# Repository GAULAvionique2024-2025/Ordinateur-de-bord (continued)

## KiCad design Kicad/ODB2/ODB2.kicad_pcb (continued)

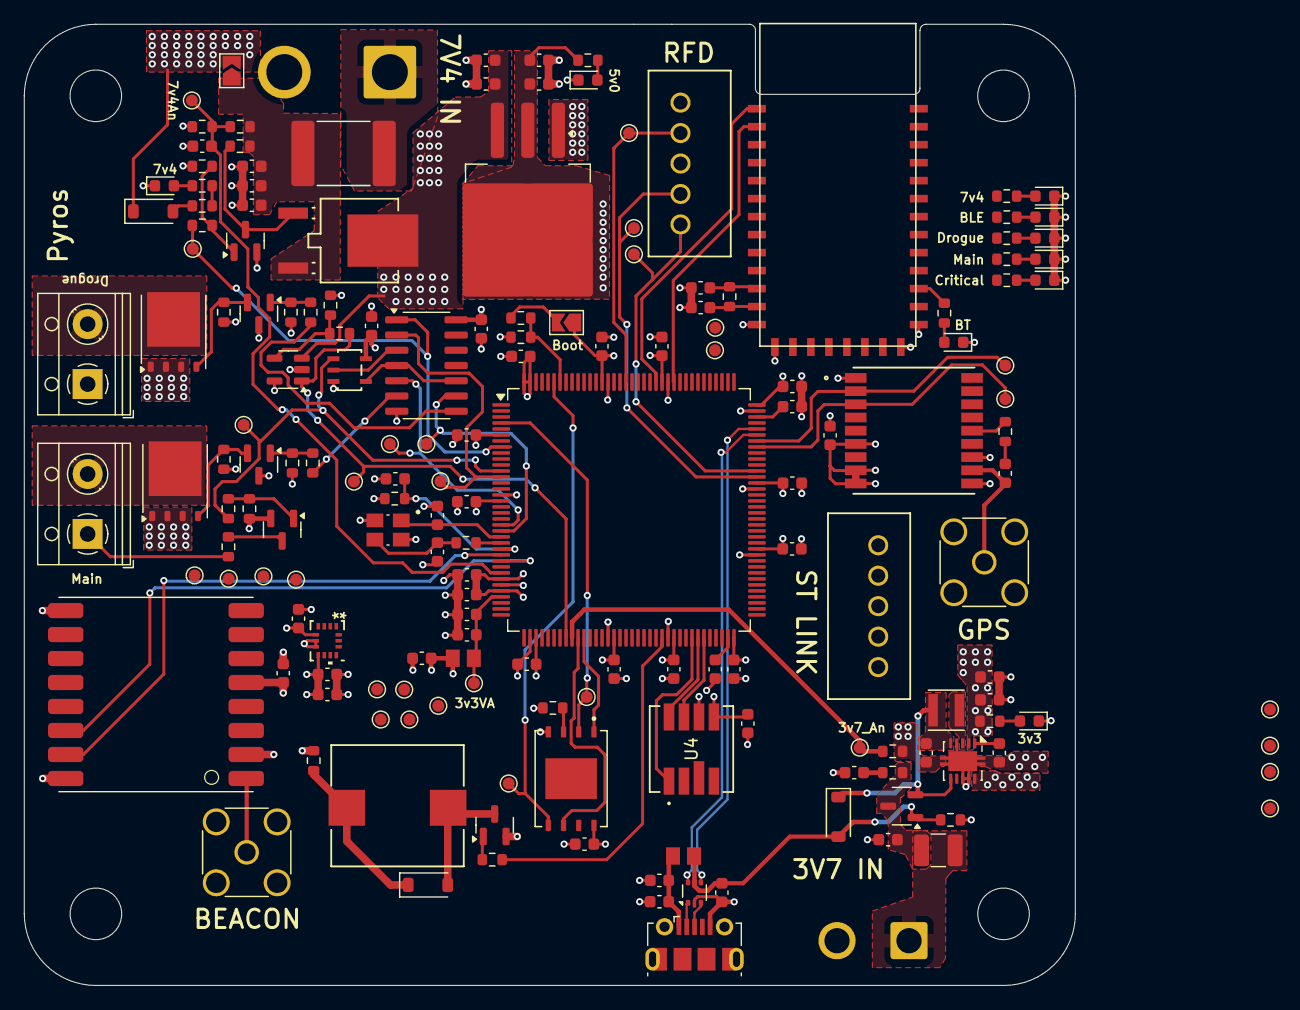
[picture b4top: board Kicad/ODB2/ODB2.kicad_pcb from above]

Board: 4 copper layers, 87.6 x 80.1 mm, 176 parts (0 on the bottom side), 101 nets.

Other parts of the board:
7v4_LED1, 7v4_LED2: GREEN; LED_0603_1608Metric

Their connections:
GND: 7v4_LED1.1 (K), 7v4_LED2.1 (K); also elsewhere on the board
unnamed 28: 7v4_LED1.2 (A); also elsewhere on the board
unnamed 29: 7v4_LED2.2 (A); also elsewhere on the board

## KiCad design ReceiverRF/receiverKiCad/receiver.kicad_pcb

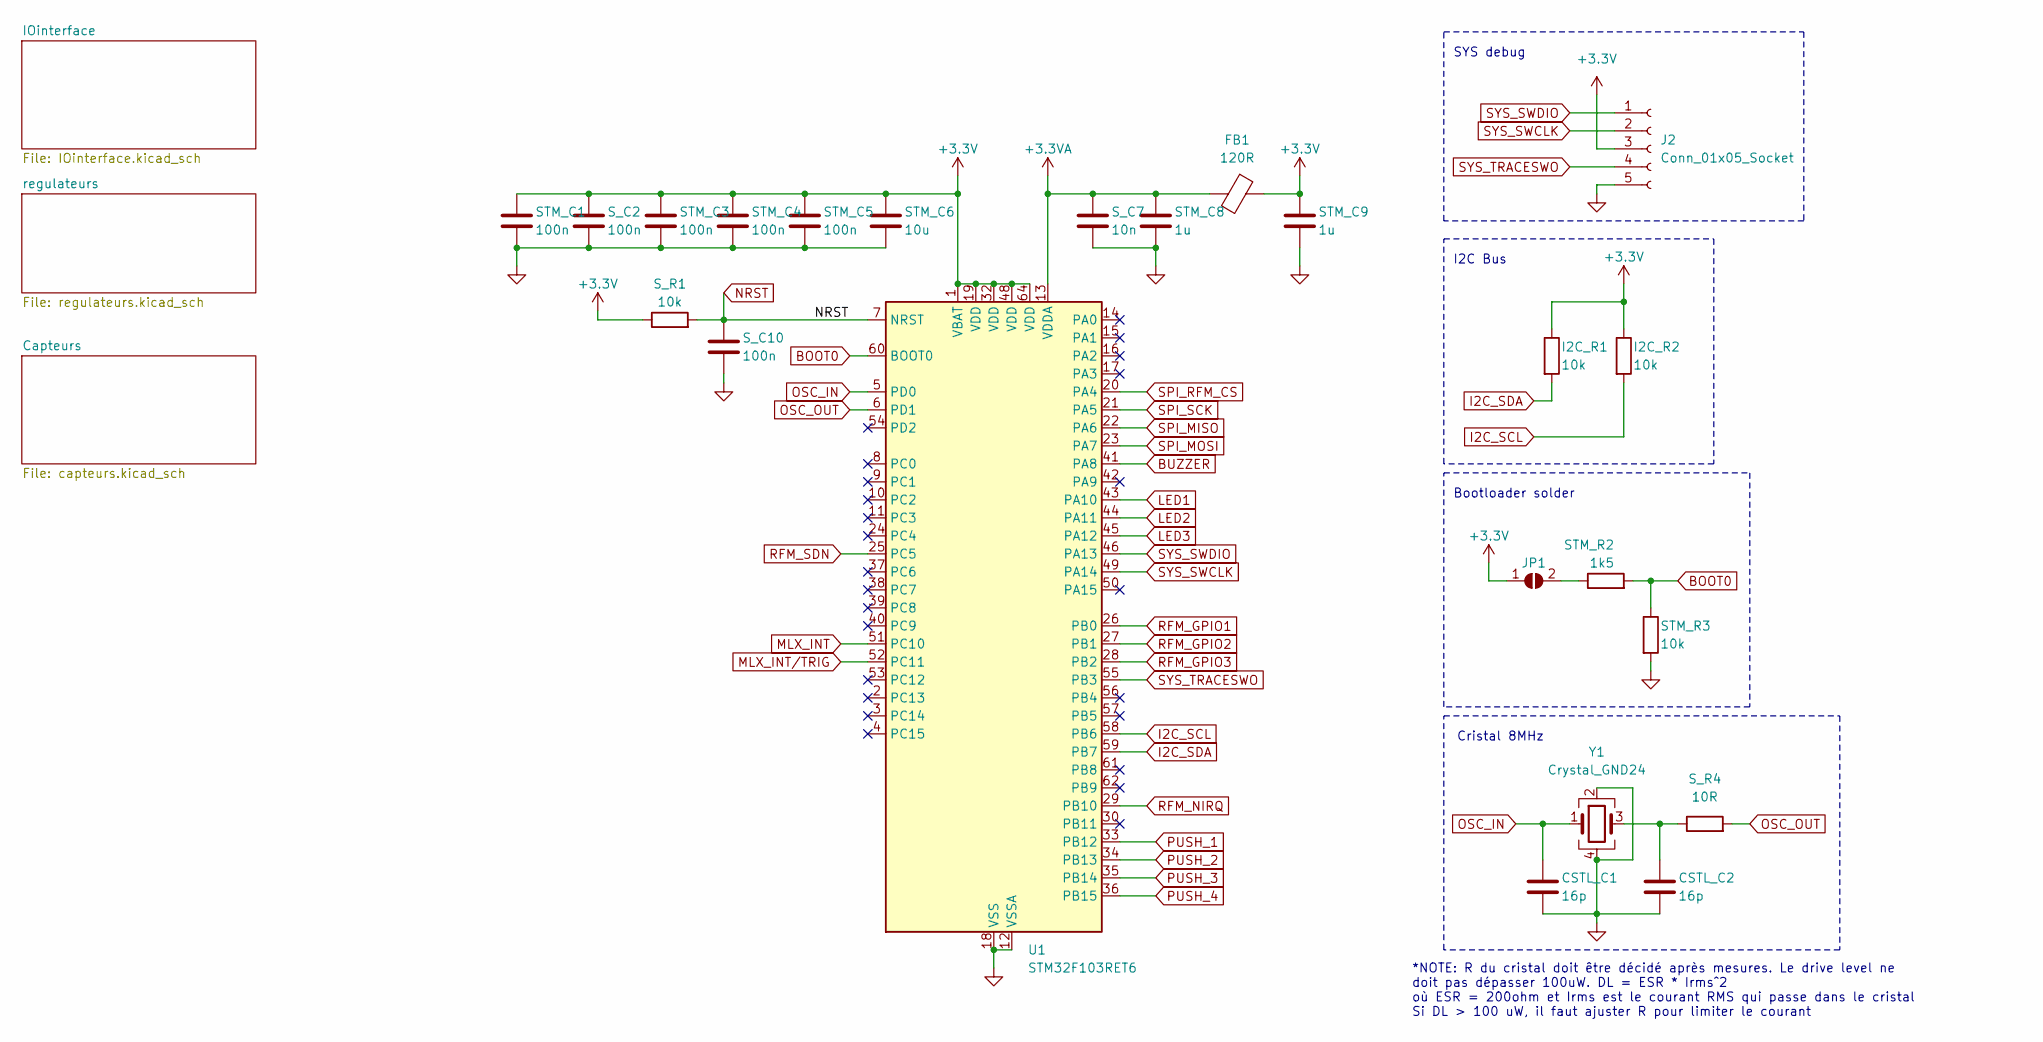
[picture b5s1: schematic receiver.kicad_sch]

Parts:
CSTL_C1, CSTL_C2: 16p; C_0402_1005Metric
FB1: 120R; Ferrite_0603
I2C_R1, I2C_R2: 10k; R_0402_1005Metric
J2: Conn_01x05_Socket; PinHeader_1x05_P2.00mm_Vertical
JP1: SolderJumper_2_Open; SolderJumper-2_P1.3mm_Open_TrianglePad1.0x1.5mm
STM_C1, STM_C3, STM_C4, STM_C5: 100n; C_0402_1005Metric
STM_C6: 10u; C_1206_3216Metric
STM_C8, STM_C9: 1u; C_0603_1608Metric
STM_R2: 1k5; R_0402_1005Metric
STM_R3: 10k; R_0402_1005Metric
S_C2, S_C10: 100n; C_0402_1005Metric
S_C7: 10n; C_0402_1005Metric
S_R1: 10k; R_0402_1005Metric
S_R4: 10R; R_0402_1005Metric
U1: STM32F103RET6; LQFP64-10x10mm
Y1: Crystal_GND24; Crystal

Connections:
+3.3V: FB1.1, I2C_R1.1, I2C_R2.1, J2.3, JP1.1 (A), STM_C1.1, STM_C3.1, STM_C4.1, STM_C5.1, STM_C6.1, STM_C9.1, S_C2.1, S_R1.1, U1.1 (VBAT), U1.19 (VDD), U1.32 (VDD), U1.48 (VDD), U1.64 (VDD); also elsewhere on the board
+3.3VA: FB1.2, STM_C8.1, S_C7.1, U1.13 (VDDA)
BOOT0: STM_R2.2, STM_R3.1, U1.60 (BOOT0)
BUZZER: U1.41 (PA8); also elsewhere on the board
GND: CSTL_C1.2, CSTL_C2.2, J2.5, STM_C1.2, STM_C3.2, STM_C4.2, STM_C5.2, STM_C6.2, STM_C8.2, STM_C9.2, STM_R3.2, S_C2.2, S_C7.2, S_C10.2, U1.12 (VSSA), U1.18 (VSS), U1.31 (VSS), U1.47 (VSS), U1.63 (VSS), Y1.2, Y1.4; also elsewhere on the board
I2C_SCL: I2C_R2.2, U1.58 (PB6); also elsewhere on the board
I2C_SDA: I2C_R1.2, U1.59 (PB7); also elsewhere on the board
LED1: U1.43 (PA10); also elsewhere on the board
LED2: U1.44 (PA11); also elsewhere on the board
LED3: U1.45 (PA12); also elsewhere on the board
MLX_INT: U1.51 (PC10); also elsewhere on the board
MLX_INT/TRIG: U1.52 (PC11); also elsewhere on the board
NRST: S_C10.1, S_R1.2, U1.7 (NRST)
unnamed: CSTL_C2.1, S_R4.1, Y1.3
unnamed: JP1.2 (B), STM_R2.1
OSC_IN: CSTL_C1.1, U1.5 (PD0), Y1.1
OSC_OUT: S_R4.2, U1.6 (PD1)
PUSH_1: U1.33 (PB12); also elsewhere on the board
PUSH_2: U1.34 (PB13); also elsewhere on the board
PUSH_3: U1.35 (PB14); also elsewhere on the board
PUSH_4: U1.36 (PB15); also elsewhere on the board
RFM_GPIO1: U1.26 (PB0); also elsewhere on the board
RFM_GPIO2: U1.27 (PB1); also elsewhere on the board
RFM_GPIO3: U1.28 (PB2); also elsewhere on the board
RFM_NIRQ: U1.29 (PB10); also elsewhere on the board
RFM_SDN: U1.25 (PC5); also elsewhere on the board
SPI_MISO: U1.22 (PA6); also elsewhere on the board
SPI_MOSI: U1.23 (PA7); also elsewhere on the board
SPI_RFM_CS: U1.20 (PA4); also elsewhere on the board
SPI_SCK: U1.21 (PA5); also elsewhere on the board
SYS_SWCLK: J2.2, U1.49 (PA14)
SYS_SWDIO: J2.1, U1.46 (PA13)
SYS_TRACESWO: J2.4, U1.55 (PB3)

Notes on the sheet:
I2C Bus
Cristal 8MHz
Bootloader solder
SYS debug
*NOTE: R du cristal doit être décidé après mesures. Le drive level ne doit pas dépasser 100uW. DL = ESR * Irms^2 où ESR = 200ohm et Irms est le courant RMS qui passe dans le cristal Si DL > 100 uW, il faut ajuster R pour limiter le courant

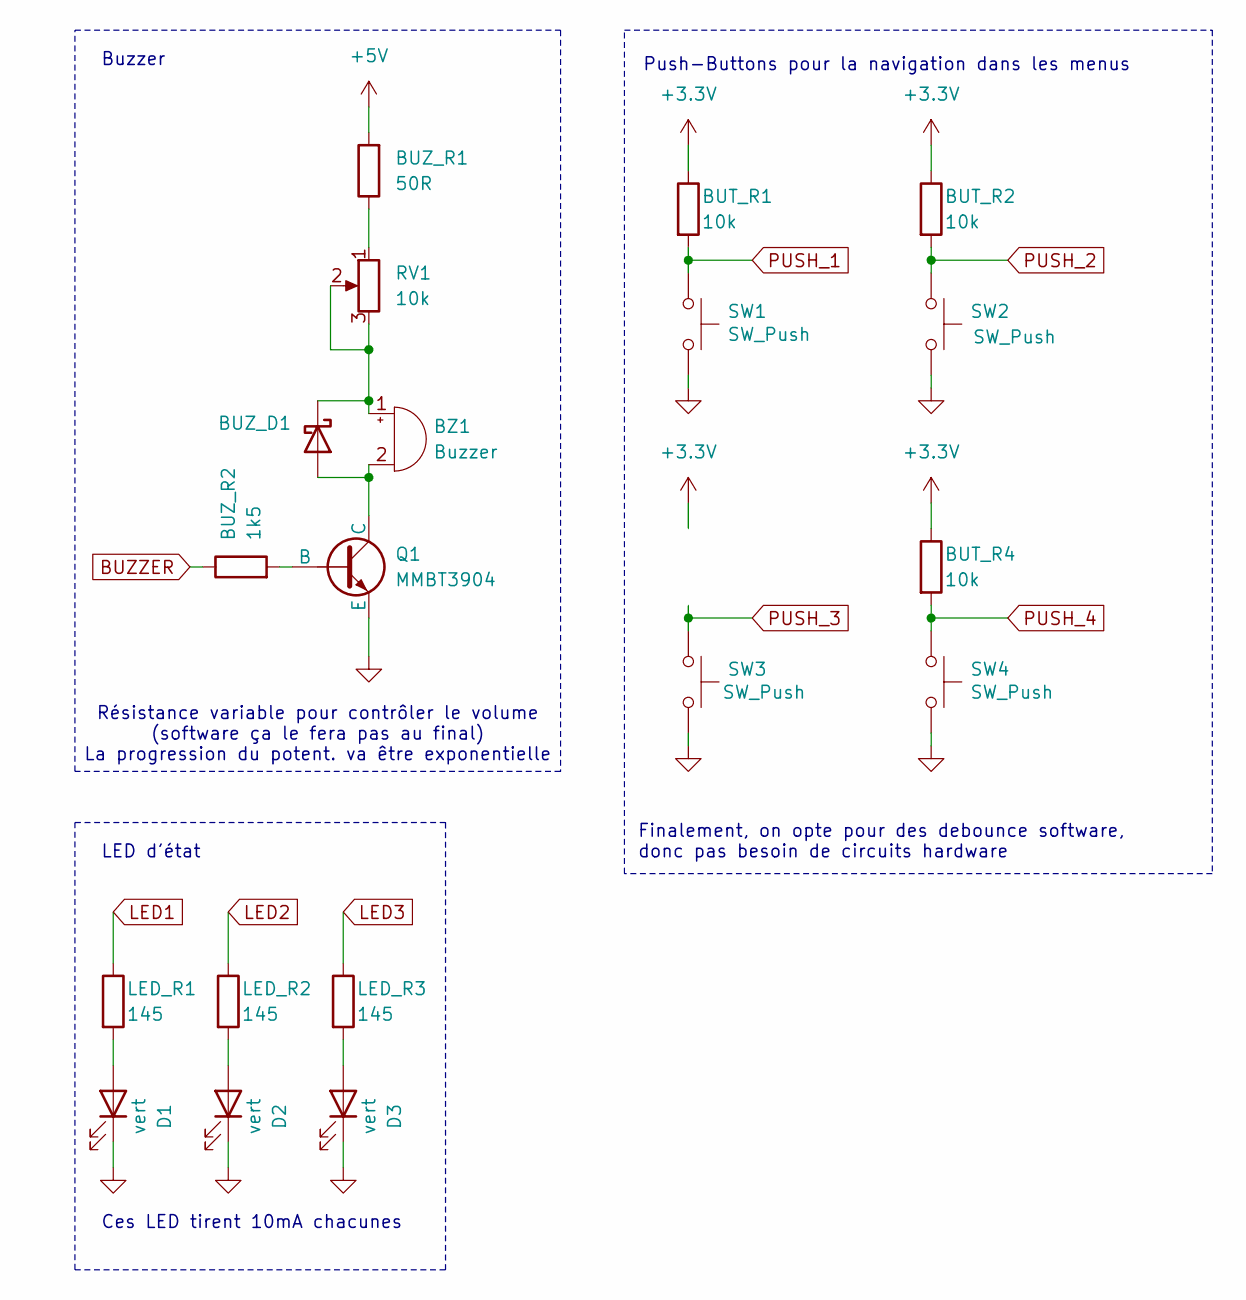
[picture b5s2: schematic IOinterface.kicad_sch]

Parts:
BUT_R1, BUT_R2, BUT_R4: 10k; R_0402_1005Metric
BUZ_D1: D_SOD-123
BUZ_R1: 50R; R_1206_3216Metric
BUZ_R2: 1k5; R_0402_1005Metric
BZ1: Buzzer; Buzzer_D14mm_H7mm_P10mm
D1, D2, D3: vert; LTST-C170GKT
LED_R1, LED_R2, LED_R3: 145; R_1206_3216Metric
Q1: MMBT3904; SOT-23
RV1: 10k; Potentiometer_Alps_RK09K_Single_Vertical
SW1, SW2, SW3, SW4: SW_Push; SW_PUSH_6mm_H4.3mm

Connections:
+3.3V: BUT_R1.1, BUT_R2.1, BUT_R4.1; also elsewhere on the board
+5V: BUZ_R1.2; also elsewhere on the board
BUZZER: BUZ_R2.1; also elsewhere on the board
GND: D1.1 (K), D2.1 (K), D3.1 (K), Q1.3 (E), SW1.2, SW2.2, SW3.2, SW4.2; also elsewhere on the board
LED1: LED_R1.1; also elsewhere on the board
LED2: LED_R2.1; also elsewhere on the board
LED3: LED_R3.1; also elsewhere on the board
unnamed: BUZ_D1.2 (A), BZ1.2 (+), Q1.1 (C)
unnamed: BUZ_D1.1 (K), BZ1.1 (-), RV1.2, RV1.3
unnamed: BUZ_R1.1, RV1.1
unnamed: D1.2 (A), LED_R1.2
unnamed: D2.2 (A), LED_R2.2
unnamed: D3.2 (A), LED_R3.2
unnamed: BUZ_R2.2, Q1.2 (B)
PUSH_1: BUT_R1.2, SW1.1; also elsewhere on the board
PUSH_2: BUT_R2.2, SW2.1; also elsewhere on the board
PUSH_3: SW3.1; also elsewhere on the board
PUSH_4: BUT_R4.2, SW4.1; also elsewhere on the board

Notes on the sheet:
Finalement, on opte pour des debounce software, donc pas besoin de circuits hardware
Résistance variable pour contrôler le volume (software ça le fera pas au final) La progression du potent. va être exponentielle
Buzzer
Ces LED tirent 10mA chacunes
Push-Buttons pour la navigation dans les menus
LED d'état

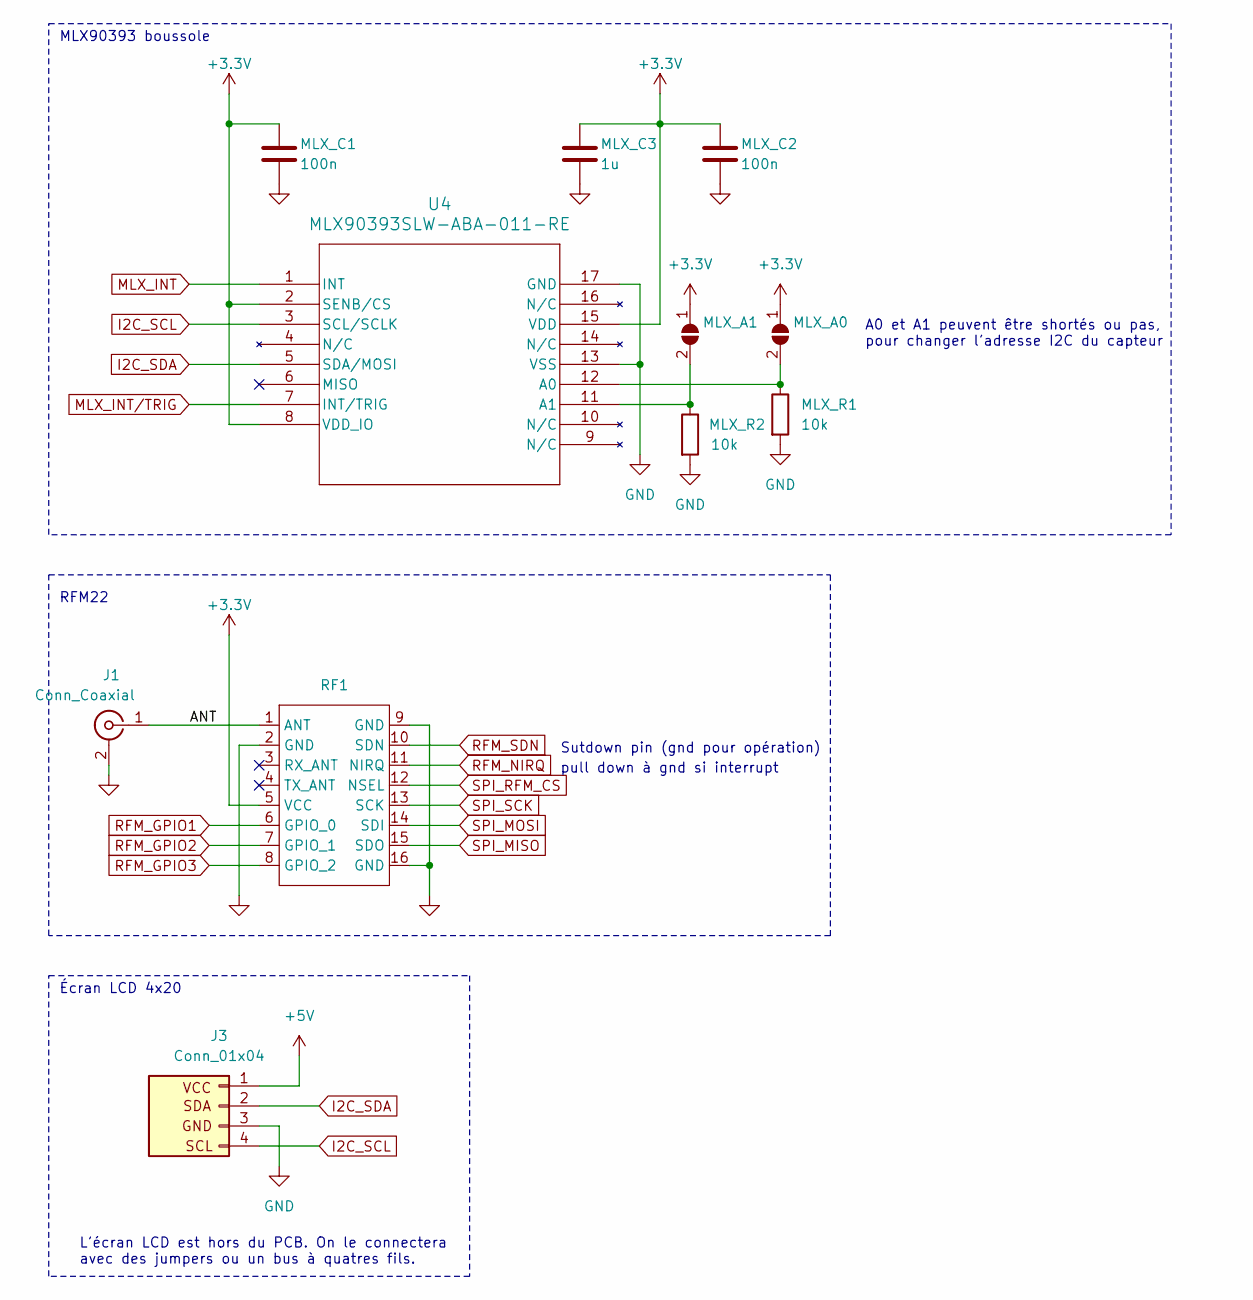
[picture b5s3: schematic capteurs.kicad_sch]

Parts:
J1: Conn_Coaxial; SMA_90deg
J3: Conn_01x04; PinHeader_1x04_P2.00mm_Vertical
MLX_A0, MLX_A1: 0; SolderJumper-2_P1.3mm_Open_TrianglePad1.0x1.5mm
MLX_C1, MLX_C2: 100n; C_0402_1005Metric
MLX_C3: 1u; C_0603_1608Metric
MLX_R1, MLX_R2: 10k; R_0402_1005Metric
RF1: RFM22b-S2
U4: MLX90393SLW-ABA-011-RE; QFN-16_MLX90393_MEL-L

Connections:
+3.3V: MLX_A0.1 (A), MLX_A1.1 (A), MLX_C1.1, MLX_C2.1, MLX_C3.1, RF1.5 (VCC), U4.2 (SENB/CS), U4.8 (VDD_IO), U4.15 (VDD); also elsewhere on the board
+5V: J3.1 (GND); also elsewhere on the board
/Capteurs/ANT: J1.1 (In), RF1.1 (ANT)
GND: J1.2 (Ext), J3.3 (SDA), MLX_C1.2, MLX_C2.2, MLX_C3.2, MLX_R1.2, MLX_R2.2, RF1.2 (GND), RF1.9 (GND), RF1.16 (GND), U4.13 (VSS), U4.17 (GND); also elsewhere on the board
I2C_SCL: J3.4 (SCL), U4.3 (SCL/SCLK); also elsewhere on the board
I2C_SDA: J3.2 (VCC), U4.5 (SDA/MOSI); also elsewhere on the board
MLX_INT: U4.1 (INT); also elsewhere on the board
MLX_INT/TRIG: U4.7 (INT/TRIG); also elsewhere on the board
unnamed: MLX_A0.2 (B), MLX_R1.1, U4.12 (A0)
unnamed: MLX_A1.2 (B), MLX_R2.1, U4.11 (A1)
RFM_GPIO1: RF1.6 (GPIO_0); also elsewhere on the board
RFM_GPIO2: RF1.7 (GPIO_1); also elsewhere on the board
RFM_GPIO3: RF1.8 (GPIO_2); also elsewhere on the board
RFM_NIRQ: RF1.11 (NIRQ); also elsewhere on the board
RFM_SDN: RF1.10 (SDN); also elsewhere on the board
SPI_MISO: RF1.15 (SDO); also elsewhere on the board
SPI_MOSI: RF1.14 (SDI); also elsewhere on the board
SPI_RFM_CS: RF1.12 (NSEL); also elsewhere on the board
SPI_SCK: RF1.13 (SCK); also elsewhere on the board

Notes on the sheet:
L'écran LCD est hors du PCB. On le connectera avec des jumpers ou un bus à quatres fils.
pull down à gnd si interrupt
Sutdown pin (gnd pour opération)
MLX90393 boussole
RFM22
A0 et A1 peuvent être shortés ou pas, pour changer l'adresse I2C du capteur
Écran LCD 4x20

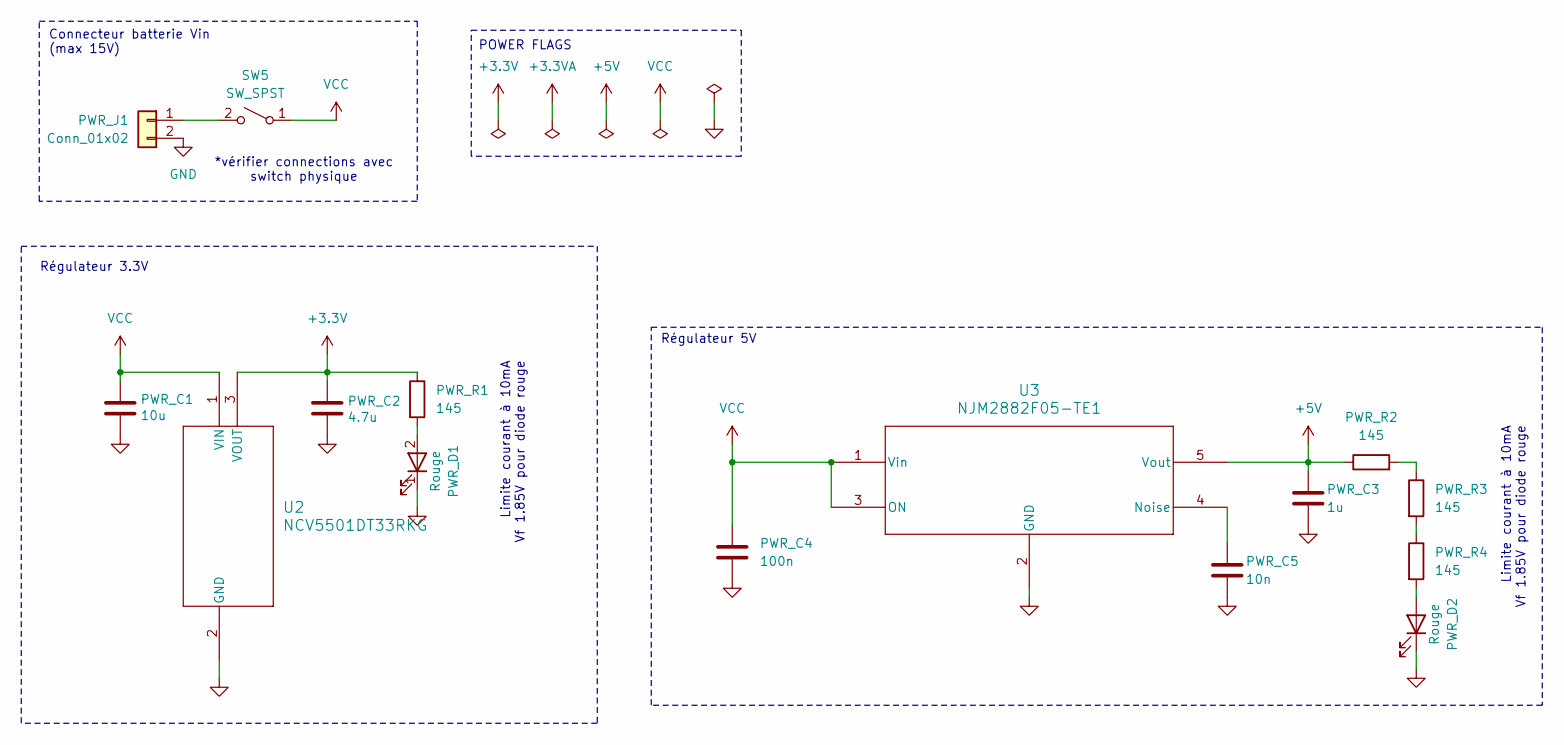
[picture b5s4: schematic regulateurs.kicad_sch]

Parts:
PWR_C1: 10u; C_1206_3216Metric
PWR_C2: 4.7u; C_0603_1608Metric
PWR_C3: 1u; C_0603_1608Metric
PWR_C4: 100n; C_0402_1005Metric
PWR_C5: 10n; C_0402_1005Metric
PWR_D1, PWR_D2: Rouge; LTST-C190EKT
PWR_J1: Conn_01x02; PinHeader_1x02_P2.00mm_Vertical
PWR_R1, PWR_R2, PWR_R3, PWR_R4: 145; R_1206_3216Metric
SW5: SW_SPST; SW_1MS02Q_CNK
U2: NCV5501DT33RKG; DPAK-3_ONS-M
U3: NJM2882F05-TE1; SOT-23-5

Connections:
+3.3V: PWR_C2.1, PWR_R1.1, U2.3 (VOUT); also elsewhere on the board
+5V: PWR_C3.1, PWR_R2.1, U3.5 (Vout); also elsewhere on the board
GND: PWR_C1.2, PWR_C2.2, PWR_C3.2, PWR_C4.2, PWR_C5.2, PWR_D1.1 (K), PWR_D2.1 (K), PWR_J1.2, U2.2 (GND), U3.2 (GND); also elsewhere on the board
unnamed: PWR_D1.2 (A), PWR_R1.2
unnamed: PWR_D2.2 (A), PWR_R4.2
unnamed: PWR_J1.1, SW5.2 (B)
unnamed: PWR_R2.2, PWR_R3.1
unnamed: PWR_R3.2, PWR_R4.1
unnamed: PWR_C5.1, U3.4 (Noise)
VCC: PWR_C1.1, PWR_C4.1, SW5.1 (A), U2.1 (VIN), U3.1 (Vin), U3.3 (ON)

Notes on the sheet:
Limite courant à 10mA Vf 1.85V pour diode rouge
Connecteur batterie Vin (max 15V)
POWER FLAGS
Régulateur 5V
*vérifier connections avec switch physique
Régulateur 3.3V

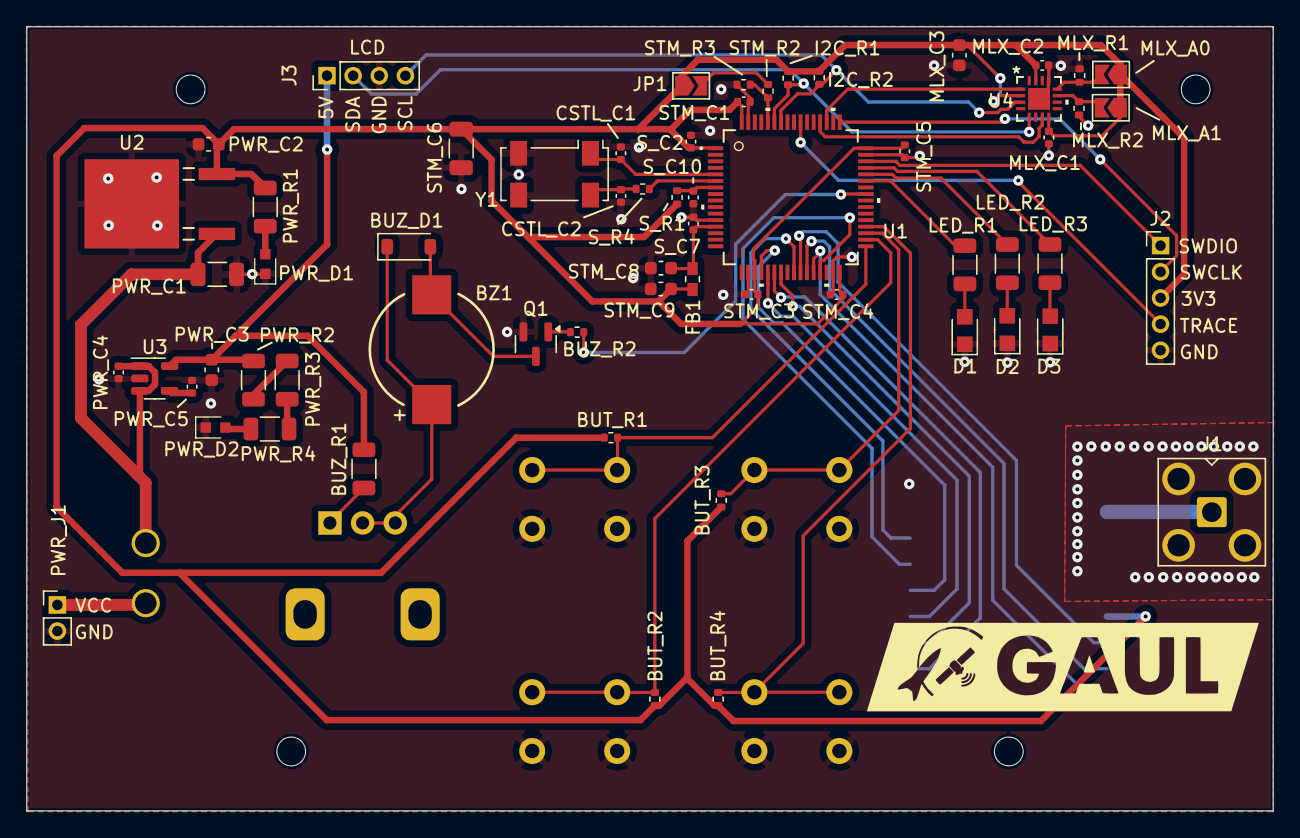
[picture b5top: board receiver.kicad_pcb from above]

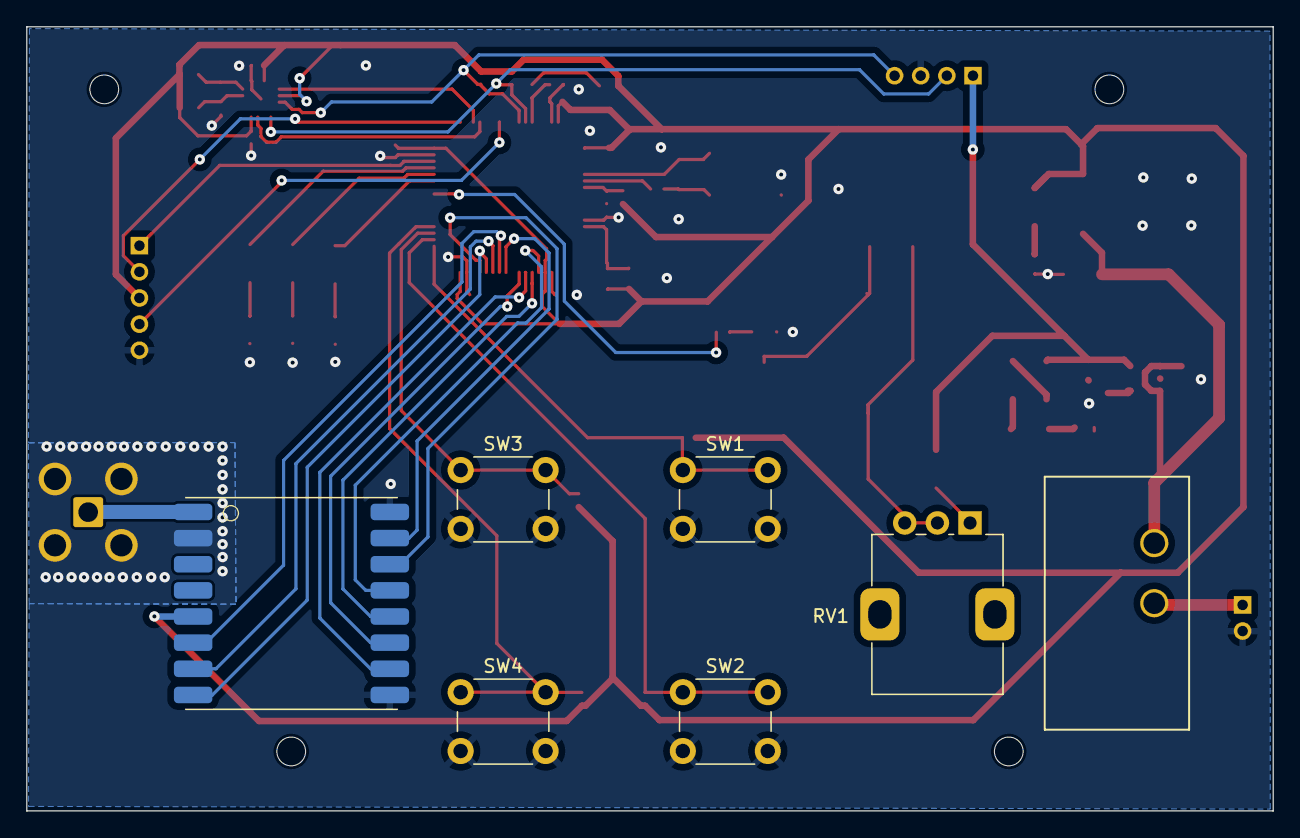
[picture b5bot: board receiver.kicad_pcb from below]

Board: 2 copper layers, 95.4 x 60.0 mm, 69 parts (7 on the bottom side), 51 nets.

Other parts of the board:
BUT_R3: 10k; R_0402_1005Metric

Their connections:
+3.3V: BUT_R3.1; also elsewhere on the board
PUSH_3: BUT_R3.2; also elsewhere on the board

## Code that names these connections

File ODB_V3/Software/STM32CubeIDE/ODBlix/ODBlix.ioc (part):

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Mcu.Name=STM32F412Z(E-G)Tx
Mcu.Package=LQFP144
Mcu.UserName=STM32F412ZGTx
PA0.GPIOParameters=GPIO_Label
PA0.GPIO_Label=PA_An
PA0.Signal=ADCx_IN0
PA1.GPIOParameters=GPIO_Label
PA1.GPIO_Label=Sense_4
PA1.Signal=ADCx_IN1
PA10.GPIOParameters=GPIO_Label
PA10.GPIO_Label=RFD_USART1_RX
PA10.Mode=Asynchronous
PA10.Signal=USART1_RX
PA11.Mode=Device_Only
PA11.Signal=USB_OTG_FS_DM
PA12.Mode=Device_Only
PA12.Signal=USB_OTG_FS_DP
PA13.GPIOParameters=GPIO_Label
PA13.GPIO_Label=SYS_SWDIO
PA13.Mode=Trace_Asynchronous_SW
PA13.Signal=SYS_JTMS-SWDIO
PA14.GPIOParameters=GPIO_Label
PA14.GPIO_Label=SYS_SWCLK
PA14.Mode=Trace_Asynchronous_SW
PA14.Signal=SYS_JTCK-SWCLK
PA2.GPIOParameters=GPIO_Label
PA2.GPIO_Label=BT_USART2_TX
PA2.Mode=Asynchronous
PA2.Signal=USART2_TX
PA3.GPIOParameters=GPIO_Label
PA3.GPIO_Label=BT_USART2_RX
PA3.Mode=Asynchronous
PA3.Signal=USART2_RX
PA4.GPIOParameters=GPIO_Label
PA4.GPIO_Label=BARO_SPI1_CS
PA4.Signal=GPIO_Output
PA5.GPIOParameters=GPIO_Label
PA5.GPIO_Label=BARO_SPI1_CLK
PA5.Mode=Full_Duplex_Master
PA5.Signal=SPI1_SCK
PA6.GPIOParameters=GPIO_Label
PA6.GPIO_Label=BARO_SPI1_MISO
PA6.Mode=Full_Duplex_Master
PA6.Signal=SPI1_MISO
PA7.GPIOParameters=GPIO_Label
PA7.GPIO_Label=BARO_SPI1_MOSI
PA7.Mode=Full_Duplex_Master
PA7.Signal=SPI1_MOSI
PA8.GPIOParameters=GPIO_Speed,GPIO_Label
PA8.GPIO_Label=ACC_I2C3_SCL
PA8.GPIO_Speed=GPIO_SPEED_FREQ_MEDIUM
PA8.Mode=I2C
PA8.Signal=I2C3_SCL
PA9.GPIOParameters=GPIO_Label
PA9.GPIO_Label=RFD_USART1_TX
PA9.Mode=Asynchronous
PA9.Signal=USART1_TX
PB0.GPIOParameters=GPIO_Label
PB0.GPIO_Label=Sense_1
PB0.Signal=ADCx_IN8
PB1.GPIOParameters=GPIO_Label
PB1.GPIO_Label=MEM_QSPI_CLK
PB1.Mode=Single Bank 1
PB1.Signal=QUADSPI_CLK
PB10.GPIOParameters=GPIO_Label
PB10.GPIO_Label=EXTEND_IO1
PB10.Signal=USART3_TX
PB11.GPIOParameters=GPIO_Label
PB11.GPIO_Label=EXTEND_IO2
PB11.Signal=USART3_RX
PB12.GPIOParameters=GPIO_Label
PB12.GPIO_Label=EXTEND_IO3
PB12.Signal=GPIO_Input
PB13.GPIOParameters=GPIO_Label
PB13.GPIO_Label=EXTEND_IO4
PB13.Signal=GPIO_Input
PB3.GPIOParameters=GPIO_Label
PB3.GPIO_Label=SYS_SWO
PB3.Mode=Trace_Asynchronous_SW
PB3.Signal=SYS_JTDO-SWO
PB4.GPIOParameters=GPIO_PuPd,GPIO_Label
PB4.GPIO_Label=IMU_INT
PB4.GPIO_PuPd=GPIO_PULLDOWN
PB4.Signal=GPXTI4
PB5.GPIOParameters=GPIO_Label
PB5.GPIO_Label=IMU_nReset
PB5.Signal=GPIO_Output
PB6.GPIOParameters=GPIO_Speed,GPIO_Label
PB6.GPIO_Label=IMU_I2C1_SCL
PB6.GPIO_Speed=GPIO_SPEED_FREQ_MEDIUM
PB6.Mode=I2C
PB6.Signal=I2C1_SCL
PB7.GPIOParameters=GPIO_Speed,GPIO_Label
PB7.GPIO_Label=IMU_I2C1_SDA
PB7.GPIO_Speed=GPIO_SPEED_FREQ_MEDIUM
PB7.Mode=I2C
PB7.Signal=I2C1_SDA
PC0.GPIOParameters=GPIO_Label
PC0.GPIO_Label=TEMP_An
PC0.Signal=ADCx_IN10
PC1.GPIOParameters=GPIO_Label
PC1.GPIO_Label=Vin_An
PC1.Signal=ADCx_IN11
PC2.GPIOParameters=GPIO_Label
PC2.GPIO_Label=V5_An
PC2.Signal=ADCx_IN12
PC3.GPIOParameters=GPIO_Label
PC3.GPIO_Label=V3_An
PC3.Signal=ADCx_IN13
PC4.GPIOParameters=GPIO_Label
PC4.GPIO_Label=Sense_3
PC4.Signal=ADCx_IN14
PC5.GPIOParameters=GPIO_Label
PC5.GPIO_Label=Sense_2
PC5.Signal=ADCx_IN15
PC6.GPIOParameters=GPIO_Label
PC6.GPIO_Label=GPS_USART6_TX
PC6.Mode=Asynchronous
PC6.Signal=USART6_TX
PC7.GPIOParameters=GPIO_Label
PC7.GPIO_Label=GPS_USART6_RX
PC7.Mode=Asynchronous
PC7.Signal=USART6_RX
PC8.GPIOParameters=GPIO_Label
PC8.GPIO_Label=USB_5V
PC8.Signal=GPIO_Input
PC9.GPIOParameters=GPIO_Speed,GPIO_Label
PC9.GPIO_Label=ACC_I2C3_SDA
PC9.GPIO_Speed=GPIO_SPEED_FREQ_MEDIUM
PC9.Mode=I2C
PC9.Signal=I2C3_SDA
PD12.GPIOParameters=GPIO_Label
PD12.GPIO_Label=BUZZER_PWM
PD12.Signal=S_TIM4_CH1
PE11.GPIOParameters=GPIO_Label
PE11.GPIO_Label=SD_SPI5_CS
PE11.Signal=GPIO_Output
PE12.GPIOParameters=GPIO_Label
PE12.GPIO_Label=SD_SPI5_CLK
PE12.Mode=Full_Duplex_Master
PE12.Signal=SPI5_SCK
PE13.GPIOParameters=GPIO_Label
PE13.GPIO_Label=SD_SPI5_MISO
PE13.Mode=Full_Duplex_Master
PE13.Signal=SPI5_MISO
PE14.GPIOParameters=GPIO_Label
PE14.GPIO_Label=SD_SPI5_MOSI
PE14.Mode=Full_Duplex_Master
PE14.Signal=SPI5_MOSI
PE9.GPIOParameters=GPIO_Label
PE9.GPIO_Label=Power_Good
PE9.Signal=GPIO_Input
PF0.GPIOParameters=GPIO_Speed,GPIO_Label
PF0.GPIO_Label=IDEFIX_I2C2_SDA
PF0.GPIO_Speed=GPIO_SPEED_FREQ_MEDIUM
PF0.Mode=I2C
PF0.Signal=I2C2_SDA
PF1.GPIOParameters=GPIO_Speed,GPIO_Label
PF1.GPIO_Label=IDEFIX_I2C2_SCL
PF1.GPIO_Speed=GPIO_SPEED_FREQ_MEDIUM
PF1.Mode=I2C
PF1.Signal=I2C2_SCL
PF11.GPIOParameters=GPIO_Label
PF11.GPIO_Label=Pyros_CTN
PF11.Signal=GPIO_Output
PF12.GPIOParameters=GPIO_Label
PF12.GPIO_Label=Pyros_Arm
PF12.Signal=GPIO_Output
PF13.GPIOParameters=GPIO_Label
PF13.GPIO_Label=Fire_4
PF13.Signal=GPIO_Output
PF14.GPIOParameters=GPIO_Label
PF14.GPIO_Label=Fire_3
PF14.Signal=GPIO_Output
PF15.GPIOParameters=GPIO_Label
PF15.GPIO_Label=Fire_2
PF15.Signal=GPIO_Output
PF2.GPIOParameters=GPIO_Label
PF2.GPIO_Label=CriticalLED_G
PF2.Signal=GPIO_Output
PF3.GPIOParameters=GPIO_Label
PF3.GPIO_Label=CriticalLED_R
PF3.Signal=GPIO_Output
PF6.GPIOParameters=GPIO_Label
PF6.GPIO_Label=MEM_QSPI_IO3
PF6.Mode=Single Bank 1
PF6.Signal=QUADSPI_BK1_IO3
PF7.GPIOParameters=GPIO_Label
PF7.GPIO_Label=MEM_QSPI_IO2
PF7.Mode=Single Bank 1
PF7.Signal=QUADSPI_BK1_IO2
PF8.GPIOParameters=GPIO_Label
PF8.GPIO_Label=MEM_QSPI_IO0
PF8.Mode=Single Bank 1
PF8.Signal=QUADSPI_BK1_IO0
PF9.GPIOParameters=GPIO_Label
PF9.GPIO_Label=MEM_QSPI_IO1
PF9.Mode=Single Bank 1
PF9.Signal=QUADSPI_BK1_IO1
PG0.GPIOParameters=GPIO_Label
PG0.GPIO_Label=Fire_1
PG0.Signal=GPIO_Output
PG6.GPIOParameters=GPIO_Label
PG6.GPIO_Label=MEM_QSPI_CS
PG6.Mode=Single Bank 1
PG6.Signal=QUADSPI_BK1_NCS
PH0\ -\ OSC_IN.Mode=HSE-External-Oscillator
PH0\ -\ OSC_IN.Signal=RCC_OSC_IN
PH1\ -\ OSC_OUT.Mode=HSE-External-Oscillator
PH1\ -\ OSC_OUT.Signal=RCC_OSC_OUT
RCC.HSE_VALUE=25000000
RCC.SYSCLKFreq_VALUE=96000000
RCC.SYSCLKSource=RCC_SYSCLKSOURCE_PLLCLK
board=custom

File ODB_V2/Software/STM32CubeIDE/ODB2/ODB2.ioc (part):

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Mcu.Name=STM32F412Z(E-G)Tx
Mcu.Package=LQFP144
Mcu.UserName=STM32F412ZGTx
PA10.GPIOParameters=GPIO_Speed,GPIO_Label
PA10.GPIO_Label=GPS_RX
PA10.GPIO_Speed=GPIO_SPEED_FREQ_HIGH
PA10.Mode=Asynchronous
PA10.Signal=USART1_RX
PA11.GPIOParameters=GPIO_Label
PA11.GPIO_Label=USBData-
PA11.Mode=Device_Only
PA11.Signal=USB_OTG_FS_DM
PA12.GPIOParameters=GPIO_Label
PA12.GPIO_Label=USBData+
PA12.Mode=Device_Only
PA12.Signal=USB_OTG_FS_DP
PA13.GPIOParameters=GPIO_Label
PA13.GPIO_Label=SYS_SWDIO
PA13.Mode=Trace_Asynchronous_SW
PA13.Signal=SYS_JTMS-SWDIO
PA14.GPIOParameters=GPIO_Label
PA14.GPIO_Label=SYS_SWCLK
PA14.Mode=Trace_Asynchronous_SW
PA14.Signal=SYS_JTCK-SWCLK
PA2.GPIOParameters=PinState,GPIO_Label
PA2.GPIO_Label=RFM_CS
PA2.PinState=GPIO_PIN_RESET
PA2.Signal=GPIO_Output
PA3.GPIOParameters=GPIO_Label
PA3.GPIO_Label=ICM_INT
PA3.Signal=GPIO_Input
PA4.GPIOParameters=PinState,GPIO_Label
PA4.GPIO_Label=ICM_CS
PA4.PinState=GPIO_PIN_SET
PA4.Signal=GPIO_Output
PA5.GPIOParameters=GPIO_Speed,GPIO_Label
PA5.GPIO_Label=ICM_RFM_SCK
PA5.GPIO_Speed=GPIO_SPEED_FREQ_HIGH
PA5.Mode=Full_Duplex_Master
PA5.Signal=SPI1_SCK
PA6.GPIOParameters=GPIO_Speed,GPIO_PuPd,GPIO_Label
PA6.GPIO_Label=ICM_RFM_MISO
PA6.GPIO_PuPd=GPIO_PULLDOWN
PA6.GPIO_Speed=GPIO_SPEED_FREQ_HIGH
PA6.Mode=Full_Duplex_Master
PA6.Signal=SPI1_MISO
PA7.GPIOParameters=GPIO_Speed,GPIO_Label
PA7.GPIO_Label=ICM_RFM_MOSI
PA7.GPIO_Speed=GPIO_SPEED_FREQ_HIGH
PA7.Mode=Full_Duplex_Master
PA7.Signal=SPI1_MOSI
PA8.GPIOParameters=GPIO_Speed,PinState,GPIO_Label
PA8.GPIO_Label=CriticalLEDEnable
PA8.GPIO_Speed=GPIO_SPEED_FREQ_HIGH
PA8.PinState=GPIO_PIN_RESET
PA8.Signal=GPIO_Output
PA9.GPIOParameters=GPIO_Speed,GPIO_Label
PA9.GPIO_Label=GPS_TX
PA9.GPIO_Speed=GPIO_SPEED_FREQ_HIGH
PA9.Mode=Asynchronous
PA9.Signal=USART1_TX
PB0.GPIOParameters=GPIO_Speed,GPIO_Label
PB0.GPIO_Label=MEM_SCLK
PB0.GPIO_Speed=GPIO_SPEED_FREQ_HIGH
PB0.Mode=Full_Duplex_Master
PB0.Signal=SPI5_SCK
PB1.GPIOParameters=PinState,GPIO_Label
PB1.GPIO_Label=MEM_CS
PB1.PinState=GPIO_PIN_SET
PB1.Signal=GPIO_Output
PB13.GPIOParameters=GPIO_Label
PB13.GPIO_Label=IO_Camera2
PB13.Signal=GPIO_Output
PB14.GPIOParameters=GPIO_Label
PB14.GPIO_Label=IO_Camera1
PB14.Signal=GPIO_Output
PB3.GPIOParameters=GPIO_Label
PB3.GPIO_Label=SYS_SWO
PB3.Mode=Trace_Asynchronous_SW
PB3.Signal=SYS_JTDO-SWO
PB8.GPIOParameters=GPIO_Speed,GPIO_Label
PB8.GPIO_Label=MEM_MOSI
PB8.GPIO_Speed=GPIO_SPEED_FREQ_HIGH
PB8.Mode=Full_Duplex_Master
PB8.Signal=SPI5_MOSI
PC0.GPIOParameters=GPIO_Label
PC0.GPIO_Label=RFM_SDN
PC0.Signal=GPIO_Output
PC1.GPIOParameters=GPIO_Label
PC1.GPIO_Label=RFM_NIRQ
PC1.Signal=GPIO_Input
PC14-OSC32_IN.GPIOParameters=GPIO_Label
PC14-OSC32_IN.GPIO_Label=Enable7v4
PC14-OSC32_IN.Signal=GPIO_Output
PC3.GPIOParameters=GPIO_Label
PC3.GPIO_Label=AN_7v4
PC3.Signal=SharedAnalog_PC3
PC4.GPIOParameters=GPIO_Label
PC4.GPIO_Label=PYROS_ADC
PC4.Signal=SharedAnalog_PC4
PC5.GPIOParameters=GPIO_Label
PC5.GPIO_Label=AN_3v7
PC5.Signal=SharedAnalog_PC5
PC6.GPIOParameters=GPIO_Speed,GPIO_Label
PC6.GPIO_Label=RFD_TX
PC6.GPIO_Speed=GPIO_SPEED_FREQ_HIGH
PC6.Mode=Asynchronous
PC6.Signal=USART6_TX
PC7.GPIOParameters=GPIO_Speed,GPIO_Label
PC7.GPIO_Label=RFD_RX
PC7.GPIO_Speed=GPIO_SPEED_FREQ_HIGH
PC7.Mode=Asynchronous
PC7.Signal=USART6_RX
PD5.GPIOParameters=GPIO_Speed,GPIO_Label
PD5.GPIO_Label=BT_TX
PD5.GPIO_Speed=GPIO_SPEED_FREQ_HIGH
PD5.Mode=Asynchronous
PD5.Signal=USART2_TX
PD6.GPIOParameters=GPIO_Speed,GPIO_Label
PD6.GPIO_Label=BT_RX
PD6.GPIO_Speed=GPIO_SPEED_FREQ_HIGH
PD6.Mode=Asynchronous
PD6.Signal=USART2_RX
PE12.GPIOParameters=GPIO_Speed,GPIO_Label
PE12.GPIO_Label=BARO_SCK
PE12.GPIO_Speed=GPIO_SPEED_FREQ_HIGH
PE12.Mode=Full_Duplex_Master
PE12.Signal=SPI4_SCK
PE13.GPIOParameters=GPIO_Speed,GPIO_PuPd,GPIO_Label
PE13.GPIO_Label=BARO_MISO
PE13.GPIO_PuPd=GPIO_NOPULL
PE13.GPIO_Speed=GPIO_SPEED_FREQ_HIGH
PE13.Mode=Full_Duplex_Master
PE13.Signal=SPI4_MISO
PE14.GPIOParameters=GPIO_Speed,GPIO_Label
PE14.GPIO_Label=BARO_MOSI
PE14.GPIO_Speed=GPIO_SPEED_FREQ_HIGH
PE14.Mode=Full_Duplex_Master
PE14.Signal=SPI4_MOSI
PE4.GPIOParameters=PinState,GPIO_Label
PE4.GPIO_Label=BARO_CS
PE4.PinState=GPIO_PIN_SET
PE4.Signal=GPIO_Output
PE5.GPIOParameters=GPIO_Speed,GPIO_PuPd,GPIO_Label
PE5.GPIO_Label=MEM_MISO
PE5.GPIO_PuPd=GPIO_PULLDOWN
PE5.GPIO_Speed=GPIO_SPEED_FREQ_HIGH
PE5.Mode=Full_Duplex_Master
PE5.Signal=SPI5_MISO
PE9.GPIOParameters=GPIO_Label
PE9.GPIO_Label=BUZZER_PWM
PE9.Signal=S_TIM1_CH1
PF10.GPIOParameters=GPIO_Speed,GPIO_Label
PF10.GPIO_Label=PYROS_DrogueODB
PF10.GPIO_Speed=GPIO_SPEED_FREQ_HIGH
PF10.Signal=GPIO_Output
PF2.GPIOParameters=GPIO_Speed,PinState,GPIO_Label
PF2.GPIO_Label=nPYROS_Test
PF2.GPIO_Speed=GPIO_SPEED_FREQ_HIGH
PF2.PinState=GPIO_PIN_SET
PF2.Signal=GPIO_Output
PF3.GPIOParameters=GPIO_Speed,GPIO_Label
PF3.GPIO_Label=PYROS_Bluetooth
PF3.GPIO_Speed=GPIO_SPEED_FREQ_HIGH
PF3.Signal=GPIO_Output
PF9.GPIOParameters=GPIO_Speed,GPIO_Label
PF9.GPIO_Label=PYROS_MainODB
PF9.GPIO_Speed=GPIO_SPEED_FREQ_HIGH
PF9.Signal=GPIO_Output
PG12.GPIOParameters=GPIO_Label
PG12.GPIO_Label=RFD_RTS
PG12.Signal=GPIO_Input
PH0\ -\ OSC_IN.Mode=HSE-External-Oscillator
PH0\ -\ OSC_IN.Signal=RCC_OSC_IN
PH1\ -\ OSC_OUT.Mode=HSE-External-Oscillator
PH1\ -\ OSC_OUT.Signal=RCC_OSC_OUT
RCC.HSE_VALUE=26000000
RCC.SYSCLKFreq_VALUE=96000000
RCC.SYSCLKSource=RCC_SYSCLKSOURCE_PLLCLK
board=custom

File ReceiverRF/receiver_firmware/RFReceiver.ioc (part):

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Mcu.Name=STM32F103R(C-D-E)Tx
Mcu.Package=LQFP64
Mcu.UserName=STM32F103RETx
PA0-WKUP.Signal=ADCx_IN0
PA10.Signal=GPIO_Output
PA11.Signal=GPIO_Output
PA12.Signal=GPIO_Output
PA13.Mode=Trace_Asynchronous_SW
PA13.Signal=SYS_JTMS-SWDIO
PA14.Mode=Trace_Asynchronous_SW
PA14.Signal=SYS_JTCK-SWCLK
PA4.Signal=SPI1_NSS
PA5.Mode=Full_Duplex_Master
PA5.Signal=SPI1_SCK
PA6.Mode=Full_Duplex_Master
PA6.Signal=SPI1_MISO
PA7.Mode=Full_Duplex_Master
PA7.Signal=SPI1_MOSI
PA8.Signal=S_TIM1_CH1
PB10.Signal=GPIO_Input
PB12.Signal=GPIO_Input
PB13.Signal=GPIO_Input
PB14.Signal=GPIO_Input
PB15.Signal=GPIO_Input
PB3.Mode=Trace_Asynchronous_SW
PB3.Signal=SYS_JTDO-TRACESWO
PB6.Mode=I2C
PB6.Signal=I2C1_SCL
PB7.Mode=I2C
PB7.Signal=I2C1_SDA
PC10.Signal=GPIO_Input
PC11.Signal=GPIO_Input
PC5.Signal=GPIO_Output
PD0-OSC_IN.Mode=HSE-External-Oscillator
PD0-OSC_IN.Signal=RCC_OSC_IN
PD1-OSC_OUT.Mode=HSE-External-Oscillator
PD1-OSC_OUT.Signal=RCC_OSC_OUT
board=custom

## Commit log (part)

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2025-04-27 Fixed printt()
2025-04-28 fix ms5803
    spi4 pas fonctionnel
2025-04-29 some low_level fixes
2025-05-04 add ODB1 L76LM33 + RFD900x
    à ajuster
2025-05-07 many fixes: crystal, ms5803 footprint, headers 2.54mm, ferrite bead 120R, fix silkscreens
2025-05-23 fix L76LM33 + NMEA
2025-05-26 fix C1/C2 crystal 8pF->15pF
2025-05-26 some fixes GPIO + SPI + ICM20948
2025-05-27 add rfm22b driver
2025-05-28 fix rfm22b
    - interrupt (TODO)
2025-06-02 fix gpio driver + rfm
2025-06-03 Test rfm cs
2025-06-14 feat!: icm42670 + 1v8 regualtor + test pads
    - reste pcb à faire
2025-09-12 repo: Update homepage link in README
2025-09-13 repo: Add V1 / V2 project in subfolder
2025-09-13 repo: Update README.md
2025-09-13 repo: Refine .gitignore to match files in subdirectories
2025-09-13 repo: Add ODB_V3 project (ODB_V2)
2025-09-13 repo: Remove Documentation and README from tracking
2025-09-13 repo: Update README with ODBlix branch information
    Added detailed documentation for the ODBlix branch including components, structure, and version details.
2025-09-14 repo: Mention adherence to Conventional Commits
2025-09-17 feat: new psu design from 5v-36v to 5v (not final)
2025-09-23 feat: change memory spi to quad spi
2025-09-23 fix: add decoupling capacitances 2 gps and set seperate gps page
2025-09-23 feat: add IdeFIX I2C connector (4 pins)
2025-09-24 feat!: first schematic
2025-09-24 fix: gnd connection, pcb approximative edge
2025-09-26 fix: switch ferrite bead filtre, add gps connector to main
2025-09-28 fix: swipe filter breakoutboard VCC to main connector side
2025-10-03 fix: change temperature sensor, readd footprint pyros and powersupply components,
2025-10-08 repo: New PSU design
2025-10-08 repo: add instruction to make continuity check
2025-10-12 feat: add kicad pinout (missing), rename BARO_SPI1_SCLK->CLK
    Missing Pinout:
    IMU_INT
    TEMP_OUT
    GPS_FUNCT_X
    BUZ_PWM
    VIN_An
2025-10-28 fix: change 26MHz crystal -> 25MHz + add feedback resistor
    feedback resistor supposes to help start of oscillation
2025-10-28 feat: add 5V_An and 3V3_An
2025-10-29 feat: add general ios, add can communication, add header connectors
2025-10-30 fix: change component attributs
2025-10-31 ajout footprint HM11
2025-10-31 fix: symbole errors and link missing footprints
2025-11-03 fix: bias + FB feedback after inductance in buck converter 5V
2025-11-03 fix: some footprints/symboles link + add criticalLed pin
2025-11-06 chore: update some footprint
2025-11-09 feat: add xt30 footprint + GT17HN-4DP-2H and make component groups
2025-11-13 fix: change vdd pinout vbus to 5V
2025-11-20 feat: position pyros
2025-11-22 feat: add breakout board mounting holes
2025-11-22 WIP: Initial rough placement of circuit blocks on PCB
2025-11-25 wip: pyro1 & pyro2
2025-11-26 WIP : Layout brouillon complet, fix pyro armement
2025-11-29 WIP : SD card under PCB, make board shorter in y axis
2025-12-01 fix: hm11 + add GND jumper to RESETB pullup
2025-12-03 fix : changer routing buck 3V3 de la couche 3V3 à AUX_PWR
2025-12-04 fix: disconnected edge
2025-12-04 wip: tuning + remove silkscreen + add 3d models
2025-12-04 wip (breakoutboard): l76lm33 schematic + start pcb
2025-12-17 fix: reoganised components on pcb
2025-12-19 wip: trace some componants
2025-12-22 wip: trace temperature sensor + add extend_IO exclusion (missing) + fix/modification components traces/position and convert some 7.85mils -> 10mils + add ODBlix and version Silkscreen + trace critica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
2025-12-23 wip: fixe trace 7.84->10 + adjustements
2025-12-23 wip: fix NetTie nets
2025-12-24 wip: fix gnd filtered zone
2025-12-24 wip: add silkscreen + add missing 3D models
2025-12-24 wip: add testpads (todo) + add MISO sd resistance + fix pyro labels
2025-12-26 wip: remove breakoutboard + add l76lm33 onboard
2025-12-28 wip: fixe sma connector
2025-12-29 wip: change red critical LED to AAKK RG LED + fixes
2025-12-30 wip: GPS position + pcb edge + silkscreens + fixes
2025-12-30 fix: return path, tests points and DRC
2025-12-30 wip: fixes + testpads connectors
2026-01-02 fix: link to homepage in README.md
2026-01-03 project: add flutter app + fixes + device id silkscreen
2026-01-03 feature : added fiducials for assembly
2026-01-04 wip : digikey part number et lien pour toutes pièces importantes (pas résistances, capacités, etc)
2026-01-04 wip: clear DRC
2026-01-04 fix: via on silkscreen, minor fix on traces and copper plane
2026-01-06 fix: fix Participants section
2026-01-10 wip : reduce BOM size to 50 SMD components
2026-01-11 wip: fix not connected VDD + traces
2026-01-11 fix: change 3k pulldown resistor in pyro to 5k
2026-01-11 feat(app): add nexus app template
2026-01-12 wip: add nrst hardware stlink + change header 01x05->01x06
2026-01-12 feat(app): add bluetooth service and use it in connection_page
2026-01-12 wip : fill all components in BOM
2026-01-13 fix(app): card mission status
2026-01-13 wip : done filling BOM, fix silkscreen, fix NRST hardware
2026-01-14 fix(app): change instantiate data_service -> multiprovider data_service instance + add getter + use parsed data in all pages + change _showBluetoothDisabledDialog in switch state
2026-01-14 wip: fixe library sma + cleanup + trace width
2026-01-14 fix(app): goodPowerState bool + add listview commands page + link listView to log + add button actions commands page + fix bluetooth transmititon function + remove ble console service instance to add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
2026-01-15 fix(app): fix typo + clear log
2026-01-18 fix(app): typos
2026-01-20 chore: add MIT License to the project
2026-03-03 fix: setup CubeMX parameters
2026-03-03 feat: add imu library + add criticalled driver + add printt + fixes rfd900x, measures
2026-03-07 fix: send uint8_t instead of uint16_t
2026-03-15 feat: added MS5611 driver
2026-04-11 feat: add mavlink config + mavlink python code + mavlink lib stm32cubeide + update rfd900x drivers for mavlink support
2026-04-12 chore!: cmake/clang generation environment
2026-04-12 feat!: fix pinout ioc + add int/dma l76lm33 rx + remove struct contraction utils.h + cleanup ringbuffer
2026-04-12 fix: readd deleted mavlink package generation
2026-04-12 feat: add hm11 driver + fix l76lm33 dma buffer + fix ringbuffer inline functions + fix extern call +
2026-04-12 fix: mavlink imu gyro / highg_acc
2026-04-12 fix: add pyros struct + fix critical_ed with generated macros + use generated macros for pyros
2026-04-13 feat?: add hm11 /'0' ignore + begin mem driver
2026-04-13 fix: adc measurements pipeline + cleaup hm11 TestConnection logic
2026-04-13 refact: adxl382 cleanup
2026-04-13 feat: add adxl382 temperature compensation + add python coeffs generator
2026-04-14 feat: add dma tx for rfd + seperate measurements compute + add mem struct + add pg check in measurements + fix bad config dma/interrupt
2026-04-16 feat: add hm11 parsing state machine for connection status feat: introduce nexus module with basic structure and definitions fix: update hm11 connection test function name for clarity fix: correct te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
2026-04-17 feat: Update mission state handling in data service for better clarity and functionality. feat: Enhance Bluetooth service to manage incoming data more effectively with buffering. feat: Modify command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
2026-04-18 fix: add pyros verification directly in driver + change system measurements voltage float -> uint16_t + fix l76lm33 uart fault +
2026-04-18 fix: flah + hm11 init fault
2026-04-18 build: Update compileSdkVersion to 36 in build.gradle files build: Upgrade Android Gradle plugin version to 8.9.1 in settings.gradle build: Update Flutter dependencies in pubspec.yaml to latest versi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
2026-04-18 fix(rfd900x/mavlink): receiver/transmitter
2026-04-18 Refactor MAVLink telemetry and pyros management
    - Updated `mavlink_test_rocket_telemetry` to include additional fields for IMU and event states.
    - Changed MAVLink version and XML hash in version headers.
    - Added ADC interrupt handling in `stm32f4xx_it.c` and corresponding initialization in `stm32f4xx_hal_msp.c`.
    - Refactored `pyros.c` to improve initialization and firing logic, including port handling.
    - Enhanced `system_measurements.c` to include ADC conversion complete callback.
    - Updated telemetry sending logic in `utils.c` to include new telemetry fields.
2026-04-20 feat: Update transmitter.py to use new MAVLink dialect for telemetry transmission feat: Implement separate telemetry sending for booster and sustainer with detailed parameters feat: Add odb_mavlink_v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
2026-04-21 fix: mavlink reception python
2026-04-25 feat!: change super loop to scheduler & fsm (not implemented) + change kalman filter to approximate velocity + add high-g worldz conversion with imu + add report bip with buzzer + add lots of TODOs /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
    fill config.h with global ODB paramters
2026-04-26 fix: optimse buzzer report
2026-04-30 fix: rfd900x command max freq
2026-05-04 feat: add altitude conversion macros and gravity constant feat: implement Kalman filter initialization and update logic feat: enhance system state management with new thresholds fix: correct temperat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
2026-05-07 fix: enhance Kalman filter implementation with float precision (no 64u unit) and cycle counting feat: add DWT cycle counter driver (get cycles in us)
2026-05-09 feat: add logger + chore: delete task file + fix: add attribute for packaging odb_data_t + fix: odb_data typo + fix: w25q driver for busy and no waiting delay for writing for ping-pong buffering + fe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
2026-05-11 feat: add tasks in scheduler
2026-05-15 fix: bno055 driver init + update flutter embedded package + feat: add remove/setactive task to scheduler + change ms -> Hz
2026-05-17 fix: logical fsm + task reorder
2026-05-17 fix:(wip): l76lm33 pull-up
2026-05-18 chore: update mavlink + fix: receiver/transmitter python + fix: update rfd config + feat: add w25q self test + fix: nmea parser + fix: flutter app fix gps display
2026-05-20 chore: clean up nexus + feat: add flash mapped memory + feat: add config sector in flash + feat: add dynamic config + fix: add logger memory map limit & protections + align sector start new flight + 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
2026-05-20 chore: cleanup hm11 struct + feat: add notification connection hm11 + connection check function + transmission power
2026-05-22 feat: add settings page + fix: HELLO frame transmission + feat: add commands for config odb + refact: factorisation of all pages + feat: add bluetooth functionnalities + chore: update flutter/package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
2026-05-23 fix: logger corrupted address
2026-05-24 refact: change directeory tools + feat: add memory-viewer + feat: addread/write usbc
    write functionnalities missing in tool
2026-05-25 fix: mavlink communication + fix: memory viewer generation app + refact: move scripts into domain folder + feat: add temprorary delay in transmit message mavlink odb
2026-05-26 fix: typos
2026-05-31 refact!: pyros, arming and system_measurements + fix: pyro continuity is powered by PA_An (temporary) + chore: cleanup W25Q init + feat: add temperature compensation for adc reading values
2026-05-31 fix rework scheduler and cleanup associated code+ feat: add idefix task
2026-05-31 fix: task name data update
2026-06-01 fix: uniformise accel unit to m/s/s + feat: add
2026-06-03 chore: update flutter package + feat: add idefix in nexus/odb/config + feat: add set preiod for task in scheduler + feat: add latest lat/lon for beacon transmission + feat: begin postflight logic + f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
2026-06-04 feat: add config erase and logger erase functions
2026-06-08 refact!: all project stm32
    Too many feat!, refact, chore and fix! to be listed
2026-06-09 fix: usb stm32
2026-06-13 feat: add elements in simulation
2026-06-14 fix: last stats/data flight address + fix: kalman P matrix symetrie + feat: add last max altitude in buzzer report + feat: add printf debug only + feat: add posix_timestamp in stats struct (not codde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
2026-06-14 feat: add events_page in nexus app and adapt odb code for that + fix: change getter logger to pointer + rename MSG_SET_CONFIG->MSG_GENERIC_DATA + feat: add size of stats struct + chore: typos +
2026-06-14 refact: seperate telemetry functions and beacon functions of odb + fix: callback fsm failsafe pyros
2026-06-14 fix: idefix communication (merge) + feat: add idefix frequency setting transmission
2026-06-14 fix: logger can write in differente page without lost data if more than 256 octets or reach the limit of a page + fix flight_duration and tim5 logic (removed interruption) + fix: add update of sensor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
2026-06-14 fix: logger buffer size and reduce delay double buffering / writting task
2026-06-15 fix: nexus debug app sdk
2026-06-15 fix: odb packaging mavlink + fix transmitter/receiver test scripts
2026-06-15 fix: pressure_pa telemetry mavlink
2026-06-15 fix: logger pushData index 32 corruption + fix: missing packed attribute + fix: padding alignement 132bytes -> 128bytes
2026-06-15 feat: add free space verification in logger init + fix!: make continious dara writing (nore more 128bytes offset) in logger task
